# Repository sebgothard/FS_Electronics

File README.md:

# Formula Student Electronics
Hardware projects for Formula Student UK competition 2024-25.

💻Github https://github.com/sebgothard/FS_Electronics

## [Precharge](Precharge)
A device to charge the tractive system such that the battery voltage doesn't damage the internals of the inverter.

<div align="center">

<p>The precharge module.</p>
</div>

## [Discharge](Discharge)
A device to discharge the tractive system, specifically a capacitor in the inverter.
<div align="center">

<p>The discharge module.</p>
</div>

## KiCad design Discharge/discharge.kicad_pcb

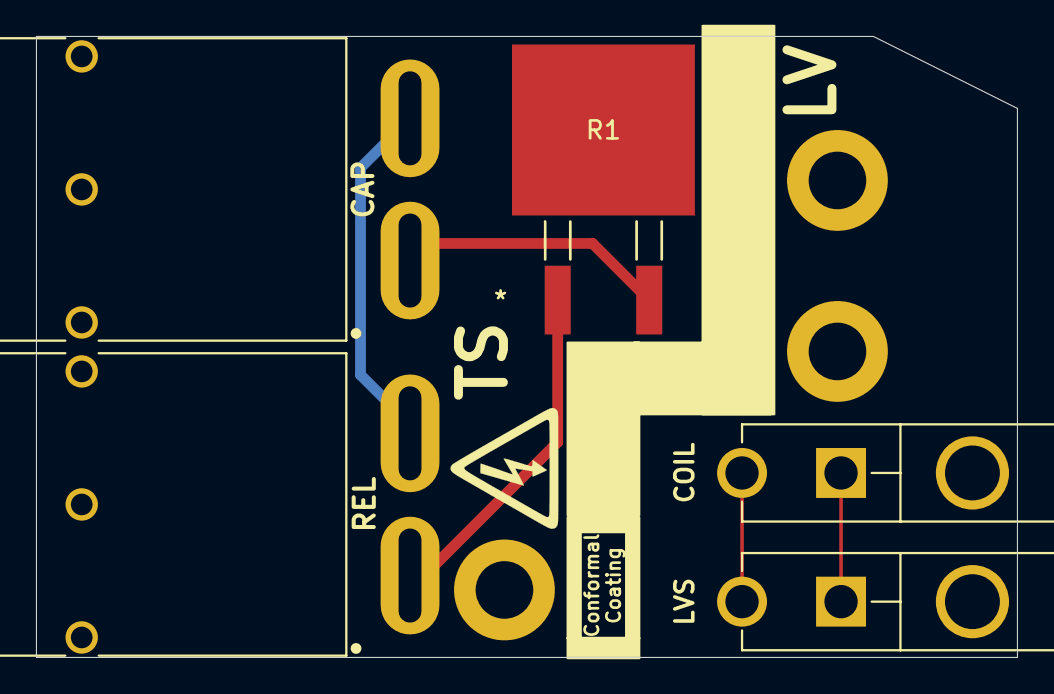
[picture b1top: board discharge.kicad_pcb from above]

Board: 2 copper layers, 54.5 x 34.5 mm, 5 parts (0 on the bottom side), 5 nets.

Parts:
CAP: HV_Conn_IN; APP_ASMPR45-1X2-RK
COIL: REL_COIL; MFJ_2X1
LVS: LV_Conn_IN; MFJ_2X1
R1: 7K5; PWR263S-35-1002F_BRN
REL: REL_SW; APP_ASMPR45-1X2-RK

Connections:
+12V: COIL.1, LVS.1
GND: COIL.2, LVS.2
INV +: CAP.1, R1.2
INV -: CAP.2, REL.2
unnamed: R1.1, REL.1

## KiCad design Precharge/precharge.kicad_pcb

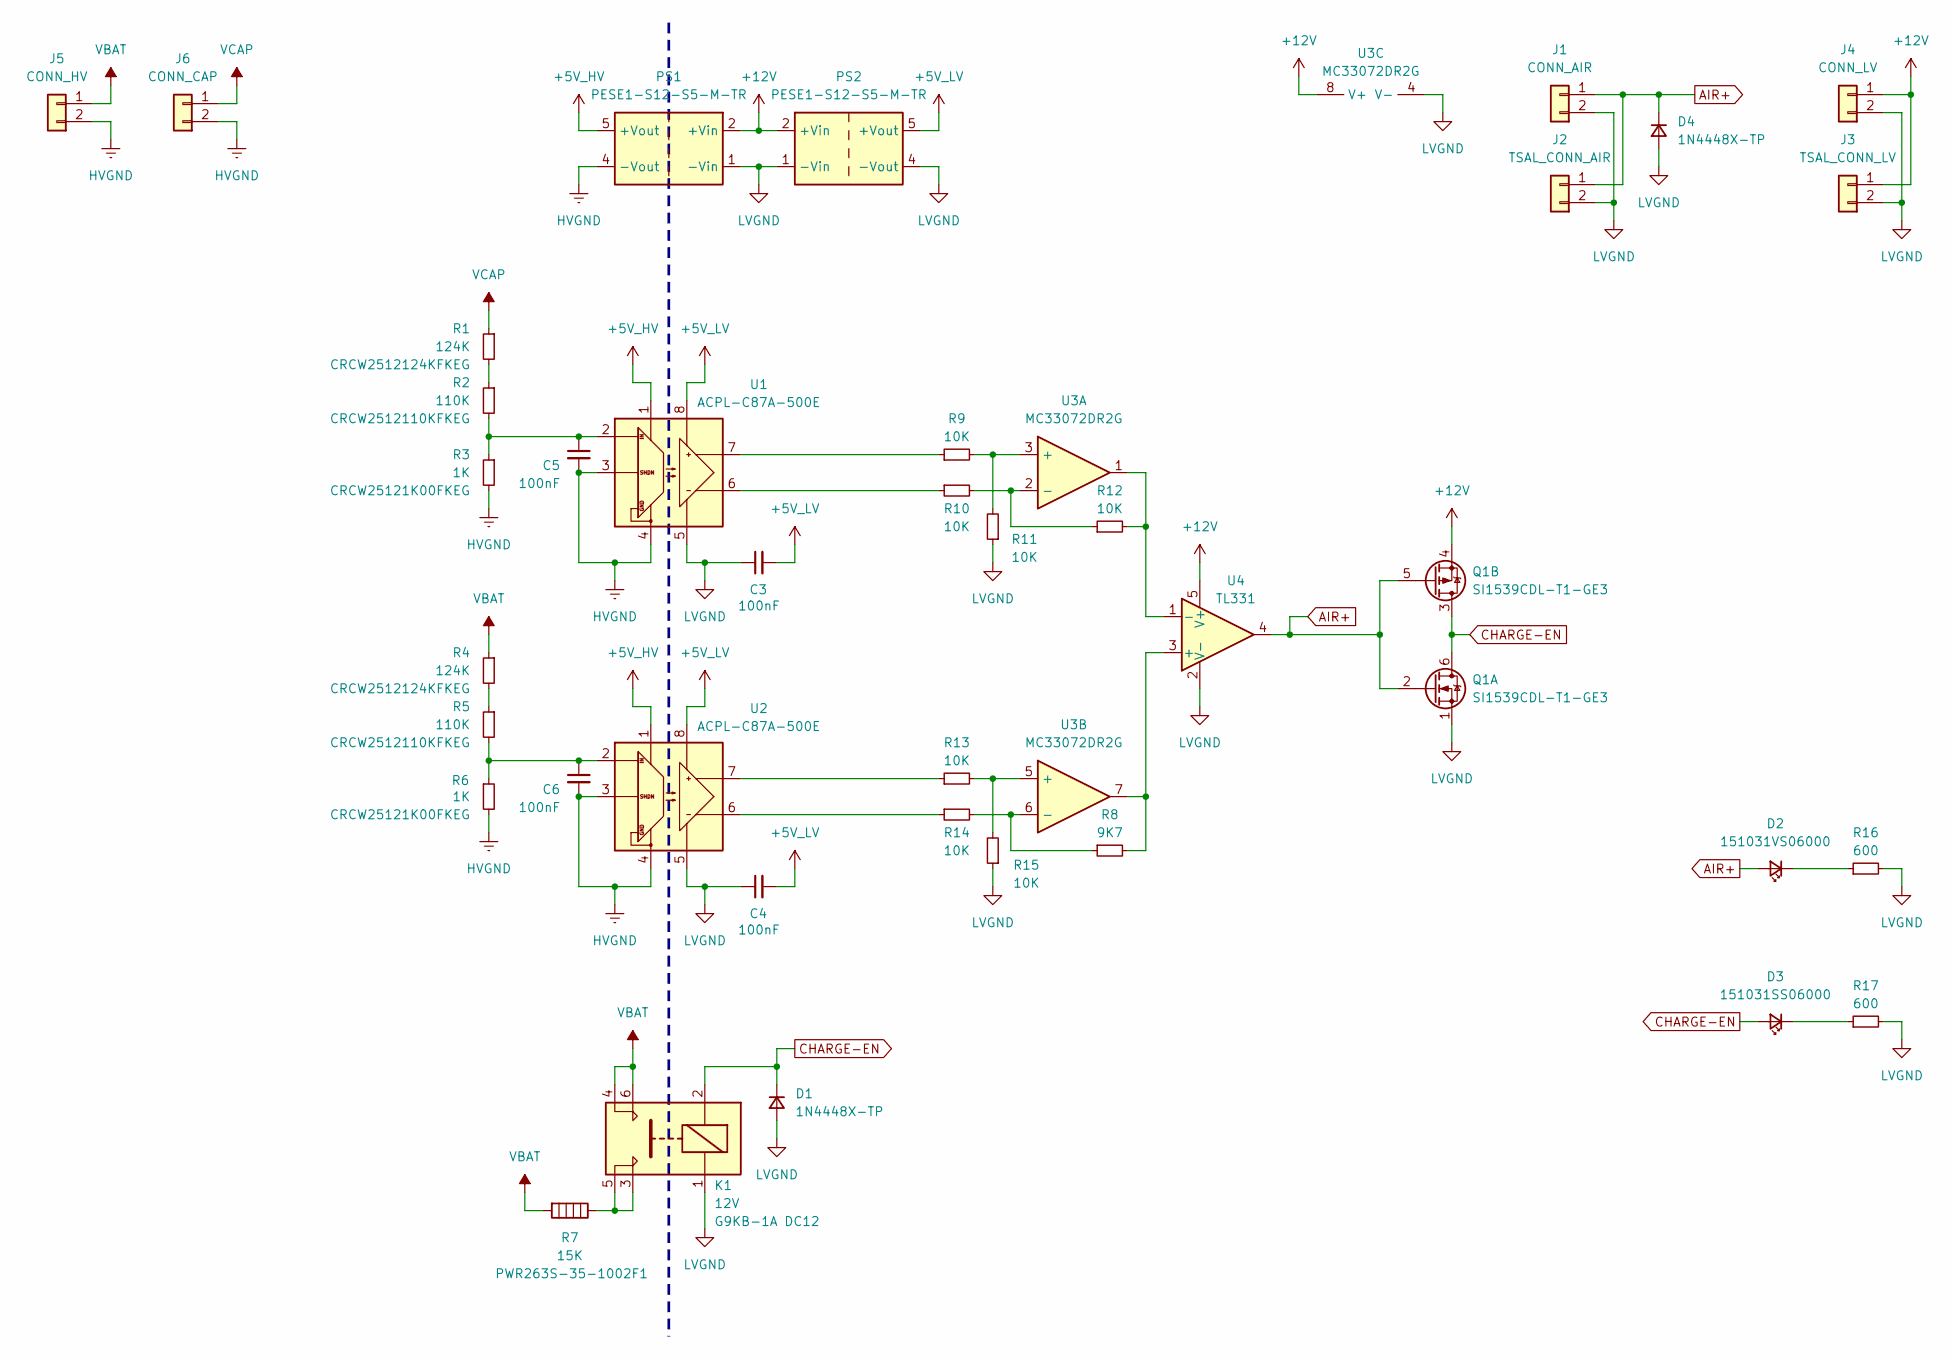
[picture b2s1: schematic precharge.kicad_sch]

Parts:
C3, C4, C5, C6: 100nF; C_0805_2012Metric
D1, D4: 1N4448X-TP; D_SOD-523
D2: 151031VS06000; WL-TMRC_3MM
D3: 151031SS06000; WL-TMRC_3MM
J1: CONN_AIR; MFJ_2X1
J2: TSAL_CONN_AIR; MFJ_2X1
J3: TSAL_CONN_LV; MFJ_2X1
J4: CONN_LV; MFJ_2X1
J5: CONN_HV; APP_ASMPR45-1X2-RK
J6: CONN_CAP; APP_ASMPR45-1X2-RK
K1: 12V; RELAY_G9KB-1A_OMR
PS1, PS2: PESE1-S12-S5-M-TR; SMD5_12.75X10.7X6.7_SINGLE_RCP
Q1: SI1539CDL-T1-GE3; SOIC-8_3.9x4.9mm_P1.27mm
R1, R4: 124K; RC2512N_VIS; Tolerance ≥1%
R2, R5: 110K; RC2512N_VIS; Tolerance ≥1%
R3, R6: 1K; RC2512N_VIS; Tolerance ≥1%
R7: 15K; PWR263S-35-1002F_BRN
R8: 9K7; R_0805_2012Metric
R9, R10, R11, R12, R13, R14, R15: 10K; R_0805_2012Metric
R16, R17: 600; R_0805_2012Metric
U1, U2: ACPL-C87A-500E; SOIC127P1150X361-8N
U3: MC33072DR2G; SOIC127P600X175-8N
U4: TL331; SOT-23-5

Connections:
+5V_HV: PS1.5 (+Vout), U1.1 (VDD1), U2.1 (VDD1)
+5V_LV: C3.2, C4.2, PS2.5 (+Vout), U1.8 (VDD2), U2.8 (VDD2)
+12V: J3.1, J4.1, PS1.2 (+Vin), PS2.2 (+Vin), Q1.4 (1), U3.8 (V+), U4.5 (V+)
AIR+: D2.2 (A), D4.1 (K), J1.1, J2.1, Q1.2 (G), Q1.5 (G), U4.4
CHARGE-EN: D1.1 (K), D3.2 (A), K1.2, Q1.3 (D), Q1.6 (D)
HVGND: C5.2, C6.2, J5.2, J6.2, PS1.4 (-Vout), R3.2, R6.2, U1.3 (IN-), U1.4 (GND1), U2.3 (IN-), U2.4 (GND1)
LVGND: C3.1, C4.1, D1.2 (A), D4.2 (A), J1.2, J2.2, J3.2, J4.2, K1.1, PS1.1 (-Vin), PS2.1 (-Vin), PS2.4 (-Vout), Q1.1 (S), R11.1, R15.1, R16.2, R17.2, U1.5 (GND2), U2.5 (GND2), U3.4 (V-), U4.2 (V-)
unnamed: D2.1 (K), R16.1
unnamed: D3.1 (K), R17.1
unnamed: K1.3, K1.5, R7.1
unnamed: R1.2, R2.1
unnamed: R4.2, R5.1
unnamed: C5.1, R2.2, R3.1, U1.2 (IN)
unnamed: R9.1, U1.7 (OUT+)
unnamed: R10.1, U1.6 (OUT-)
unnamed: C6.1, R5.2, R6.1, U2.2 (IN)
unnamed: R13.1, U2.7 (OUT+)
unnamed: R14.1, U2.6 (OUT-)
unnamed: R9.2, R11.2, U3.3 (+)
unnamed: R10.2, R12.1, U3.2 (-)
unnamed: R13.2, R15.2, U3.5 (+)
unnamed: R8.1, R14.2, U3.6 (-)
unnamed: R8.2, U3.7, U4.3 (+)
unnamed: R12.2, U3.1, U4.1 (-)

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
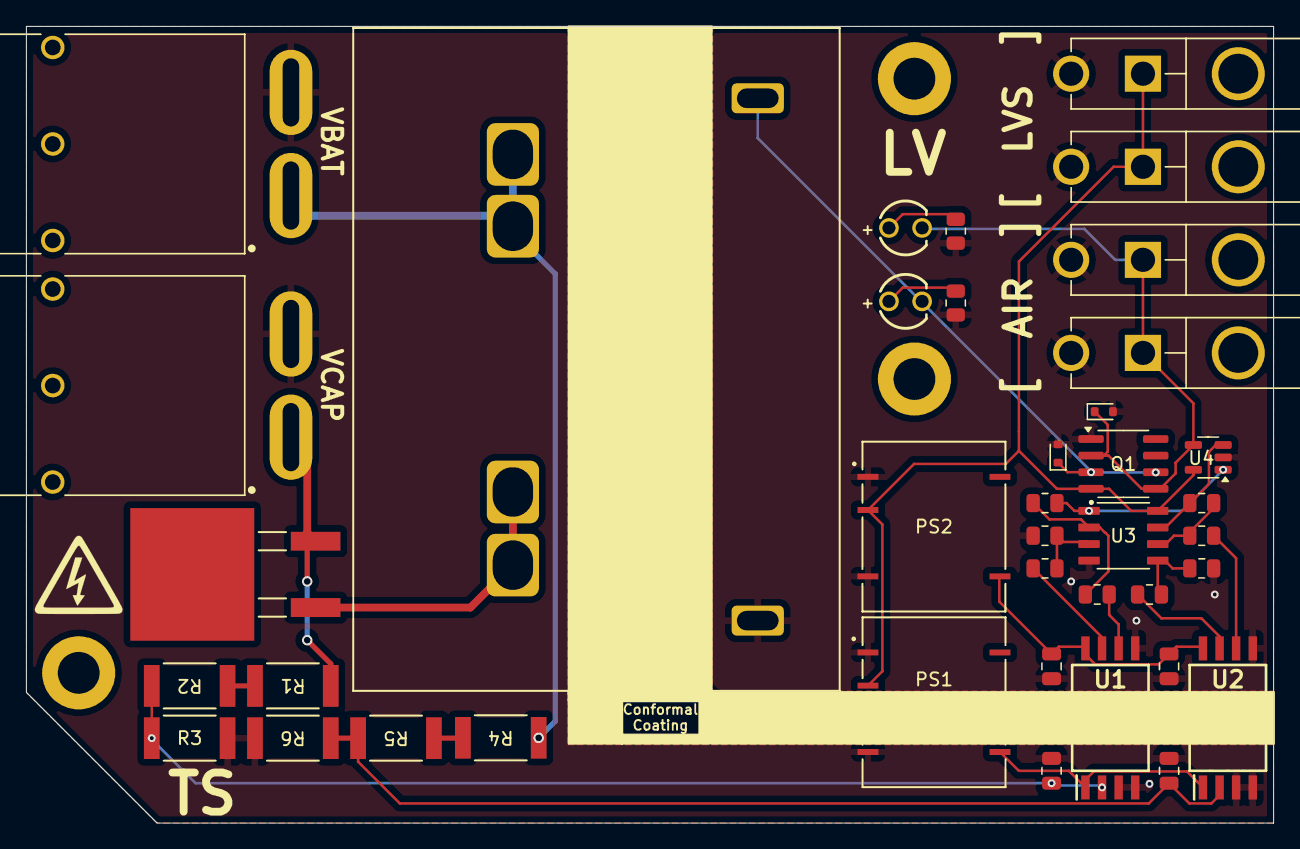
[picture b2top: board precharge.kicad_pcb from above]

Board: 2 copper layers, 95.5 x 61.0 mm, 39 parts (0 on the bottom side), 26 nets.

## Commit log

2025-08-30 Test
